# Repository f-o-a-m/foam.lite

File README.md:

# foam.lite

Deployed [here](https://f-o-a-m.github.io/foam.lite/)

## Latest Documentation

The latest documentation can be found on the [FOAM Developer Portal](https://f-o-a-m.github.io/foam.developer/foamlite/introduction.html).

## General Caveats
Due to weirdness with certain versions of Node and Spago, you'd ideally want to use the `v10.x` train of Node.
With nvm, this is `nvm install lts/dubnium && nvm use lts/dubnium`

## UI

To build the UI, make sure you have already build and deployed the dapp. When you're ready to build and serve the app, simply do

```bash
> npm i
> npm run bundle-app
> RELAYER_NFT=<contract adddress> npm run browserify
> npm run serve
```

The default address is [localhost:8080](localhost:8080)

## Quickstart to do an end-to-end flow

```shell
# Start a blockchain
make cliquebait-start

# Deploy the contracts
make deploy-contracts

# Bundle up the app to make it easier to pass arguments to it
# You could skip this step and run `spago -x <component>.dhall run -a "<args>"`
# instead of `node dist/<component>.js` in the future, but you'll have to do an
# `export PRIVATE_KEY=<copypaste the output>` as spago likes to add an annoying
# "[info] Build Succeeded" line to stdout sometimes. Also, because there's no way to tell
# spago that everything that follows is arguments for the app, you'll have to be
# wary of shell quoting/escaping issues in the `-a` arg to spago
make bundle

# Make an account that doesn't exist on the Ethereum node
PRIVATE_KEY=$(node dist/helper.js generate-private-key)
echo "The private key is ${PRIVATE_KEY}"

# Faucet the account with some of the FungibleToken we deployed, as well
# as some Ether to let it approve the RelayableNFT contract to spend its FungibleTokens
node dist/helper.js faucet --to-private-key ${PRIVATE_KEY} --also-ether

# Approve the RelayableNFT token to spend the account's balance (and automatically execute the approve() transaction on-chain)
node dist/helper.js approve --private-key ${PRIVATE_KEY} --submit --node-url "http://localhost:8545"

# Double check our balances
node dist/helper.js balance --private-key ${PRIVATE_KEY}

# Start a relayer server in the background. This is what the radios use to forward messages to the blockchain
# And what we will use to simulate radio messages being sent.
# It takes a couple of seconds to start up, so wait until you see "Started listening on http://0.0.0.0:3000"
node dist/server.js &
VALIDATE_ENDPOINT="http://localhost:3000/relay/validate"
SUBMIT_ENDPOINT="http://localhost:3000/relay/submit"

# Check the nonce that the blockchain expects our next message to have. If we've just created this account, this will probably be 0.
# You can use the output of this command as a `--nonce` argument for the `sign-*` helpers
node dist/helper.js nonce -p ${PRIVATE_KEY}

# Make a minting message that creates an "arbitrary" hello-world message
# Using relay-nonce 0, and paying 0.1 FT to the relayer, and simulate submitting it over
# the radio to our "validate" endpoint, to double check that it got encoded/signed correctly
node dist/helper.js sign-mint --private-key ${PRIVATE_KEY} -a 'Hello World!' --nonce $(node dist/helper.js nonce -p ${PRIVATE_KEY}) --fee-amount 1000000000000000000 --transmit ${VALIDATE_ENDPOINT}

# The exact same command, but to the "submit" endpoint, which will actually kick off a transaction on the blockchain
node dist/helper.js sign-mint --private-key ${PRIVATE_KEY} -a 'Hello World!' --nonce $(node dist/helper.js nonce -p ${PRIVATE_KEY}) --fee-amount 1000000000000000000 --transmit ${SUBMIT_ENDPOINT}

# We can have some fun now. Lets make a quick loop to send the current time as a relayed message on the blockchain every minute
while true; do
  the_message="It is now `date`"
  echo "sending \"${the_message}\" via relay"
  node dist/helper.js sign-mint --private-key ${PRIVATE_KEY} -a "${the_message}" --nonce $(node dist/helper.js nonce -p ${PRIVATE_KEY}) --fee-amount 1000000000000000000 --transmit ${SUBMIT_ENDPOINT}
  echo "waiting a minute" 
  sleep 60
done
```

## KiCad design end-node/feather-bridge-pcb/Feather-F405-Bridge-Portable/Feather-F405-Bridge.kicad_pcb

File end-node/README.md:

See the [latest documentation on the FOAM Developer Portal](https://f-o-a-m.github.io/foam.developer/foamlite/end-node.html) for more details and usage instructions.

**USE THIS FIRMWARE AT YOUR OWN RISK. BE MINDFUL OF LOCAL REGULATIONS PERTAINING TO USAGE OF THE RADIO SPECTRUM**

The firmware supplied here has been tested assuming all `make` commands are run with `TARGET_PLATFORM=FEATHER_F405`, which assumes an
Adafruit Feather STM32F405 Express and an RFM95W LoRa Radio FeatherWing.

While it is possible to compile for the `NUCLEO_F303RE` which can be used on the Nucleo-F303RE eval board with the SX1276MB1xAS mBed shield,
this version of the firmware with RelayableNFT functionality has not been tested on that device.

Shout outs to Trezor for making an awesome library of handy crypto utilities and all the hard work by the folks working on libsecp256k1 to make it microcontroller-friendly.

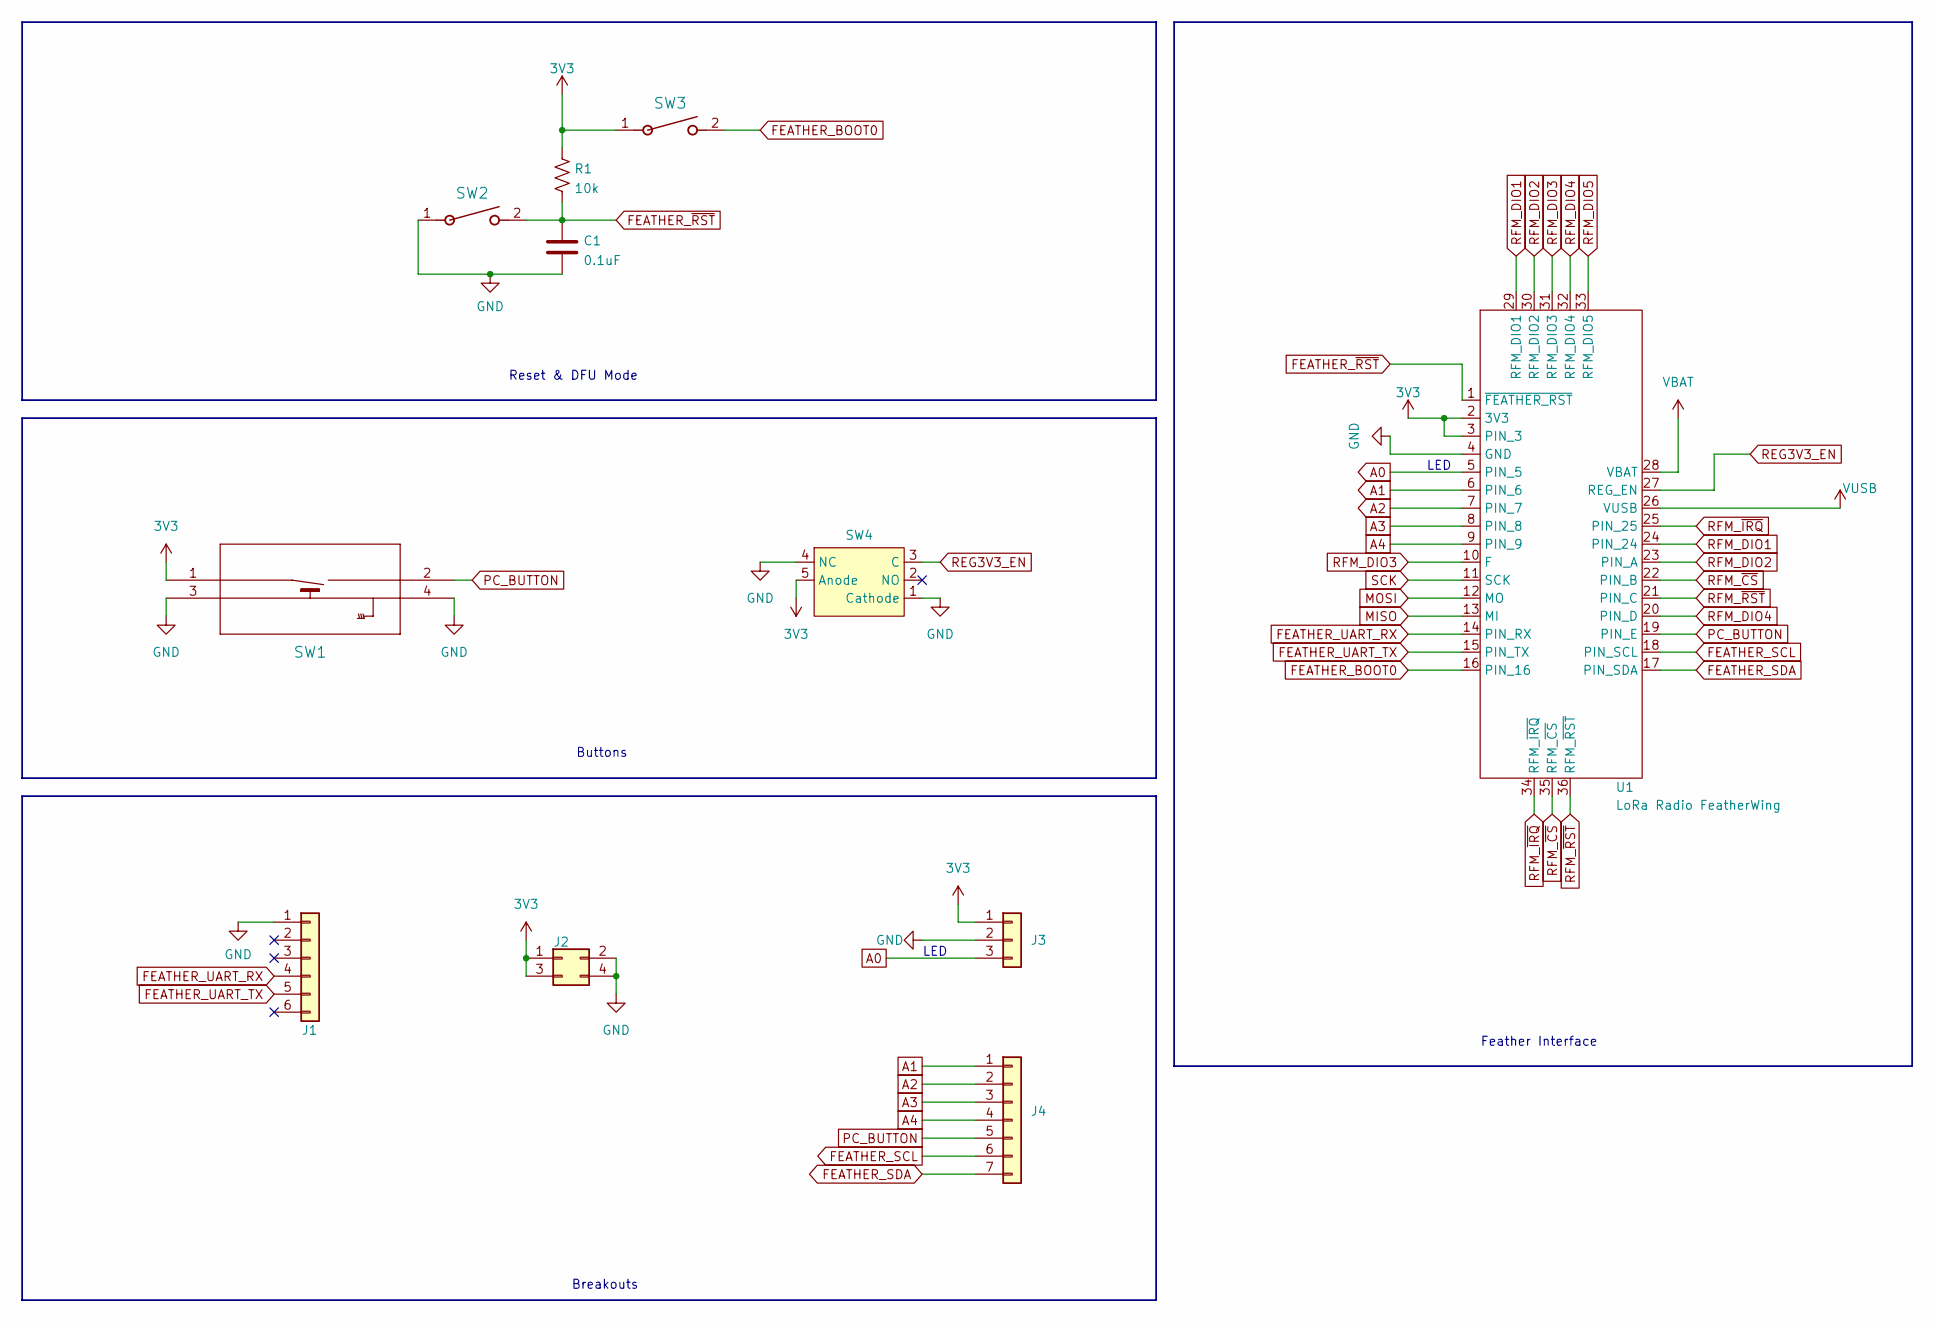
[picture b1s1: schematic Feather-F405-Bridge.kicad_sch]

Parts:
C1: 0.1uF; C_Disc_D3.0mm_W1.6mm_P2.50mm
J1: Conn_01x06; PinHeader_1x06_P2.54mm_Vertical
J2: Conn_02x02_Odd_Even; PinHeader_2x02_P2.54mm_Vertical
J3: Conn_01x03; PinHeader_1x03_P2.54mm_Vertical
J4: Conn_01x07; PinHeader_1x07_P2.54mm_Vertical
R1: 10k; R_Axial_DIN0207_L6.3mm_D2.5mm_P10.16mm_Horizontal
SW1: B3F-3152; SW_B3F-3150_OMR
SW2, SW3: TL1105MF160Q; SW_TL1105MF160Q
SW4: ELUMEETHQ7C22; ELUMEETHQC02
U1: LoRa Radio FeatherWing; Radio_FeatherWing_16x12+5+3

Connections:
3V3: J2.1, J2.3, J3.1, R1.1, SW1.1, SW3.1, SW4.5 (Anode), U1.2 (3V3), U1.3 (PIN_3)
A0: J3.3, U1.5 (PIN_5)
A1: J4.1, U1.6 (PIN_6)
A2: J4.2, U1.7 (PIN_7)
A3: J4.3, U1.8 (PIN_8)
A4: J4.4, U1.9 (PIN_9)
FEATHER_BOOT0: SW3.2, U1.16 (PIN_16)
FEATHER_SCL: J4.6, U1.18 (PIN_SCL)
FEATHER_SDA: J4.7, U1.17 (PIN_SDA)
FEATHER_UART_RX: J1.4, U1.14 (PIN_RX)
FEATHER_UART_TX: J1.5, U1.15 (PIN_TX)
FEATHER_~RST: C1.1, R1.2, SW2.2, U1.1 (~FEATHER_RST)
GND: C1.2, J1.1, J2.2, J2.4, J3.2, SW1.3, SW1.4, SW2.1, SW4.1 (Cathode), SW4.4 (NC), U1.4 (GND)
MISO: U1.13 (MI)
MOSI: U1.12 (MO)
PC_BUTTON: J4.5, SW1.2, U1.19 (PIN_E)
REG3V3_EN: SW4.3 (C), U1.27 (REG_EN)
RFM_DIO1: U1.24 (PIN_24), U1.29 (RFM_DIO1)
RFM_DIO2: U1.23 (PIN_A), U1.30 (RFM_DIO2)
RFM_DIO3: U1.10 (F), U1.31 (RFM_DIO3)
RFM_DIO4: U1.20 (PIN_D), U1.32 (RFM_DIO4)
RFM_DIO5: U1.33 (RFM_DIO5)
RFM_~CS: U1.22 (PIN_B), U1.35 (RFM_~CS)
RFM_~IRQ: U1.25 (PIN_25), U1.34 (RFM_~IRQ)
RFM_~RST: U1.21 (PIN_C), U1.36 (RFM_~RST)
SCK: U1.11 (SCK)
VBAT: U1.28 (VBAT)
VUSB: U1.26 (VUSB)

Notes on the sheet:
Reset & DFU Mode
Buttons
LED
Breakouts
Feather Interface

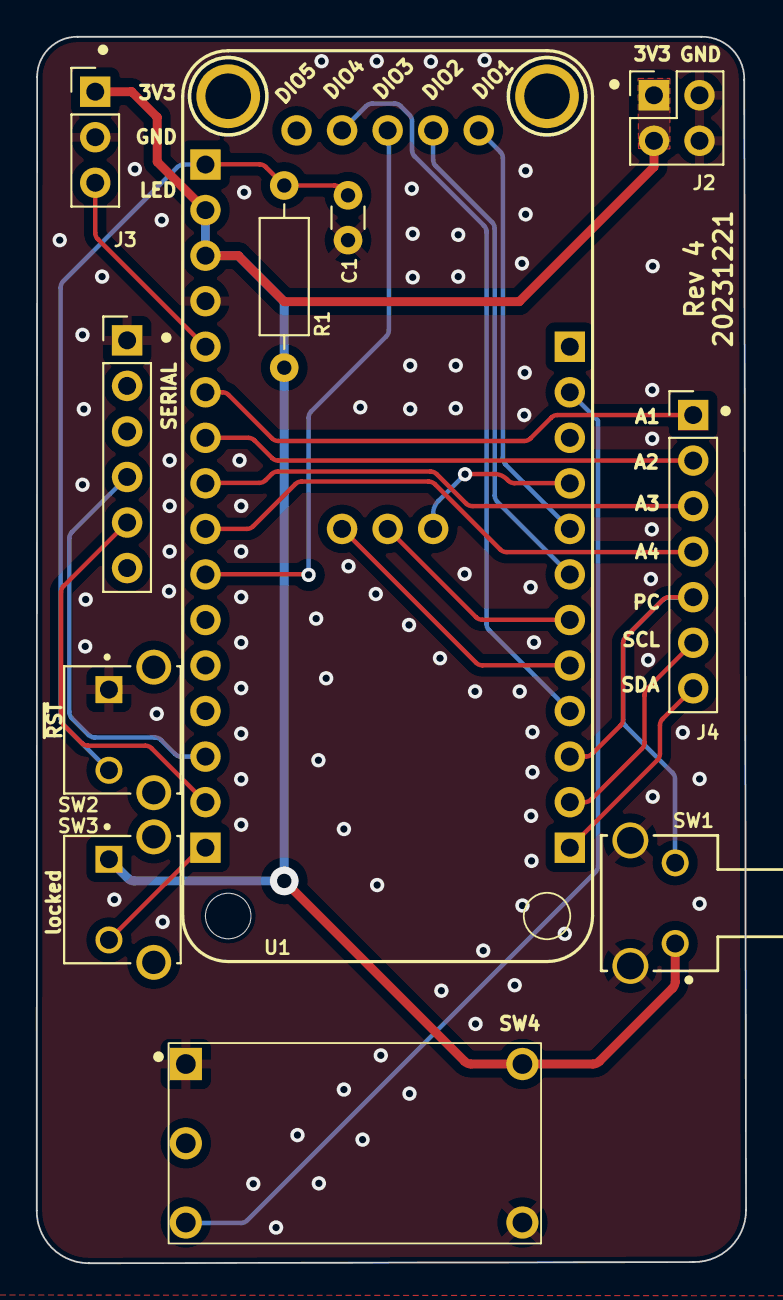
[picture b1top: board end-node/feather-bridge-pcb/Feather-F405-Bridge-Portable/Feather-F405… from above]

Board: 2 copper layers, 39.6 x 68.4 mm, 11 parts (0 on the bottom side), 22 nets.

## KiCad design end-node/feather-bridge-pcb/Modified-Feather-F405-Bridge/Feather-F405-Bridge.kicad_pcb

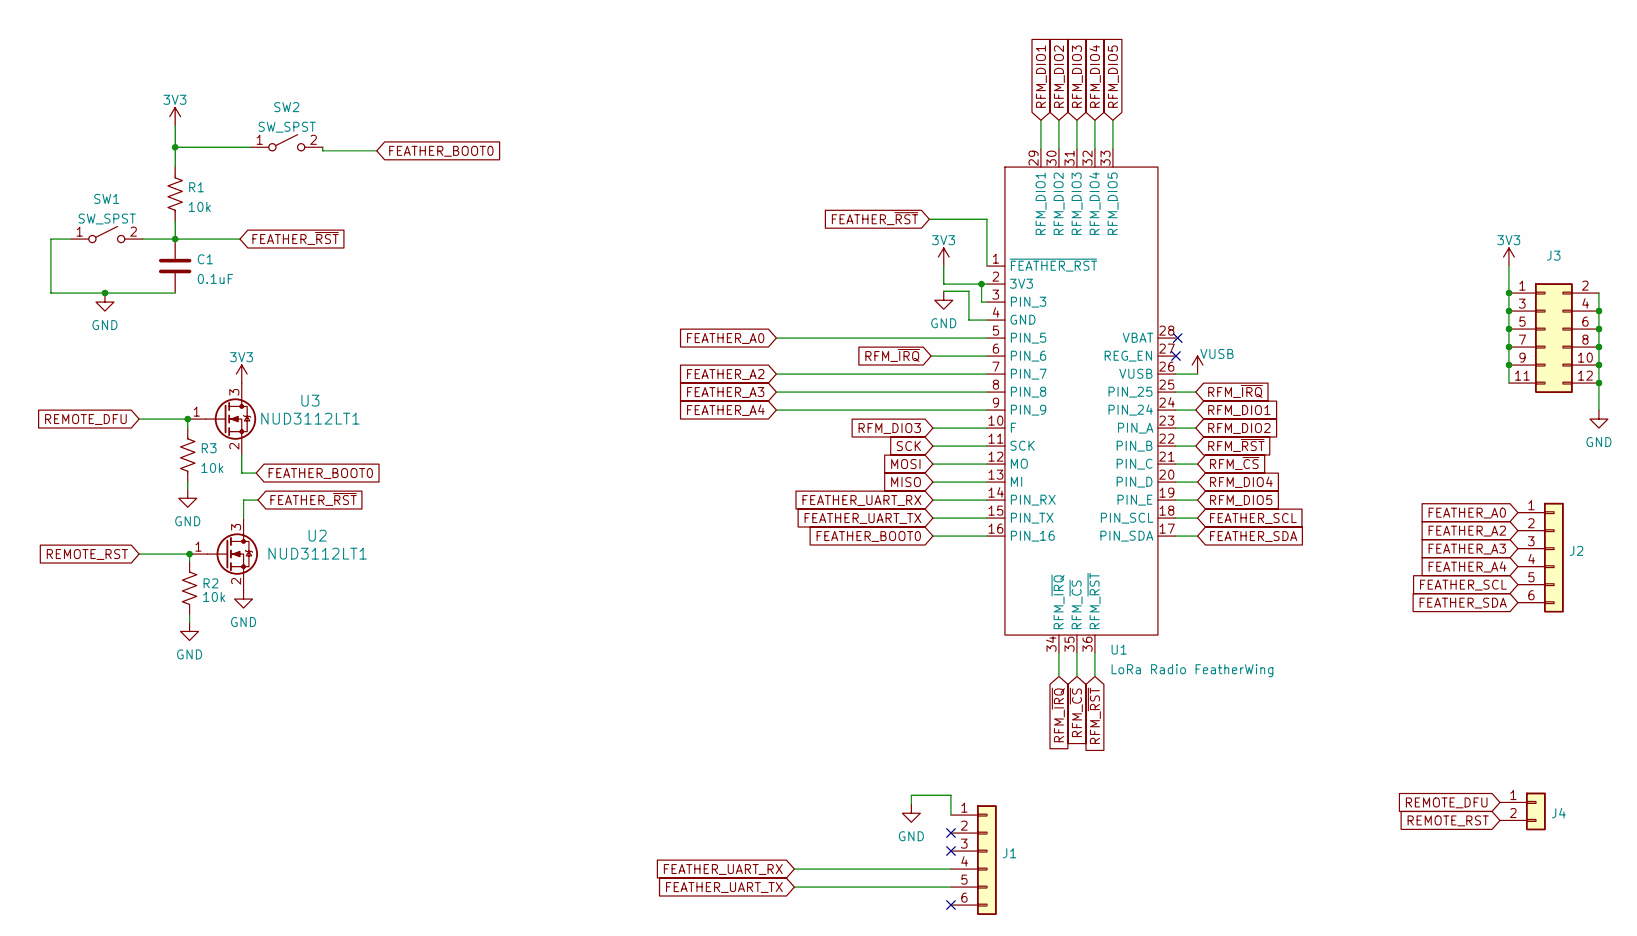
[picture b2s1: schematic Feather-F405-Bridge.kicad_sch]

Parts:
C1: 0.1uF; C_Disc_D3.0mm_W1.6mm_P2.50mm
J1, J2: Conn_01x06; PinHeader_1x06_P2.54mm_Vertical
J3: Conn_02x06_Odd_Even; PinSocket_2x06_P2.54mm_Vertical_No_Index
J4: PinHeader_1x02_P2.54mm_Horizontal
R1, R2, R3: 10k; R_Axial_DIN0207_L6.3mm_D2.5mm_P10.16mm_Horizontal
SW1, SW2: SW_SPST; SW_PUSH_6mm_THT
U1: LoRa Radio FeatherWing; Radio_FeatherWing_16x12+5+3
U2, U3: NUD3112LT1; SOT-23

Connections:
3V3: J3.1, J3.3, J3.5, J3.7, J3.9, J3.11, R1.1, SW2.1 (A), U1.2 (3V3), U1.3 (PIN_3), U3.3 (D)
FEATHER_A0: J2.1, U1.5 (PIN_5)
FEATHER_A2: J2.2, U1.7 (PIN_7)
FEATHER_A3: J2.3, U1.8 (PIN_8)
FEATHER_A4: J2.4, U1.9 (PIN_9)
FEATHER_BOOT0: SW2.2 (B), U1.16 (PIN_16), U3.2 (S)
FEATHER_SCL: J2.5, U1.18 (PIN_SCL)
FEATHER_SDA: J2.6, U1.17 (PIN_SDA)
FEATHER_UART_RX: J1.4, U1.14 (PIN_RX)
FEATHER_UART_TX: J1.5, U1.15 (PIN_TX)
FEATHER_~RST: C1.1, R1.2, SW1.2 (B), U1.1 (~FEATHER_RST), U2.3 (D)
GND: C1.2, J1.1, J3.2, J3.4, J3.6, J3.8, J3.10, J3.12, R2.1, R3.2, SW1.1 (A), U1.4 (GND), U2.2 (S)
MISO: U1.13 (MI)
MOSI: U1.12 (MO)
REMOTE_DFU: J4.1, R3.1, U3.1 (G)
REMOTE_RST: J4.2, R2.2, U2.1 (G)
RFM_DIO1: U1.24 (PIN_24), U1.29 (RFM_DIO1)
RFM_DIO2: U1.23 (PIN_A), U1.30 (RFM_DIO2)
RFM_DIO3: U1.10 (F), U1.31 (RFM_DIO3)
RFM_DIO4: U1.20 (PIN_D), U1.32 (RFM_DIO4)
RFM_DIO5: U1.19 (PIN_E), U1.33 (RFM_DIO5)
RFM_~CS: U1.21 (PIN_C), U1.35 (RFM_~CS)
RFM_~IRQ: U1.6 (PIN_6), U1.25 (PIN_25), U1.34 (RFM_~IRQ)
RFM_~RST: U1.22 (PIN_B), U1.36 (RFM_~RST)
SCK: U1.11 (SCK)
VUSB: U1.26 (VUSB)

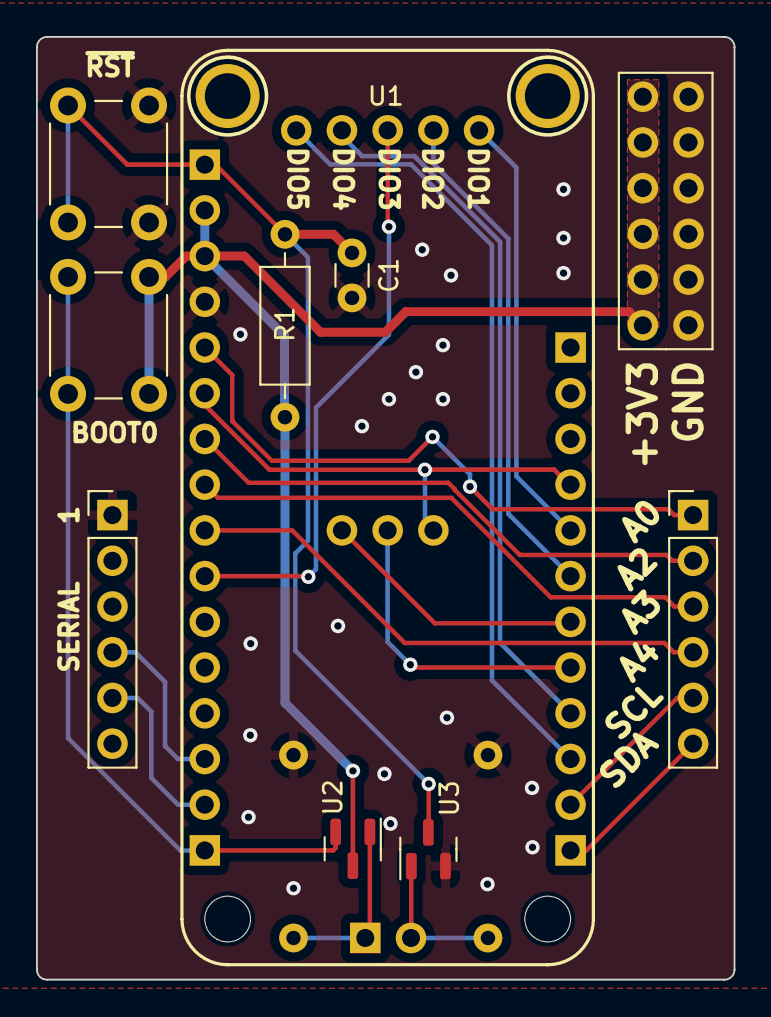
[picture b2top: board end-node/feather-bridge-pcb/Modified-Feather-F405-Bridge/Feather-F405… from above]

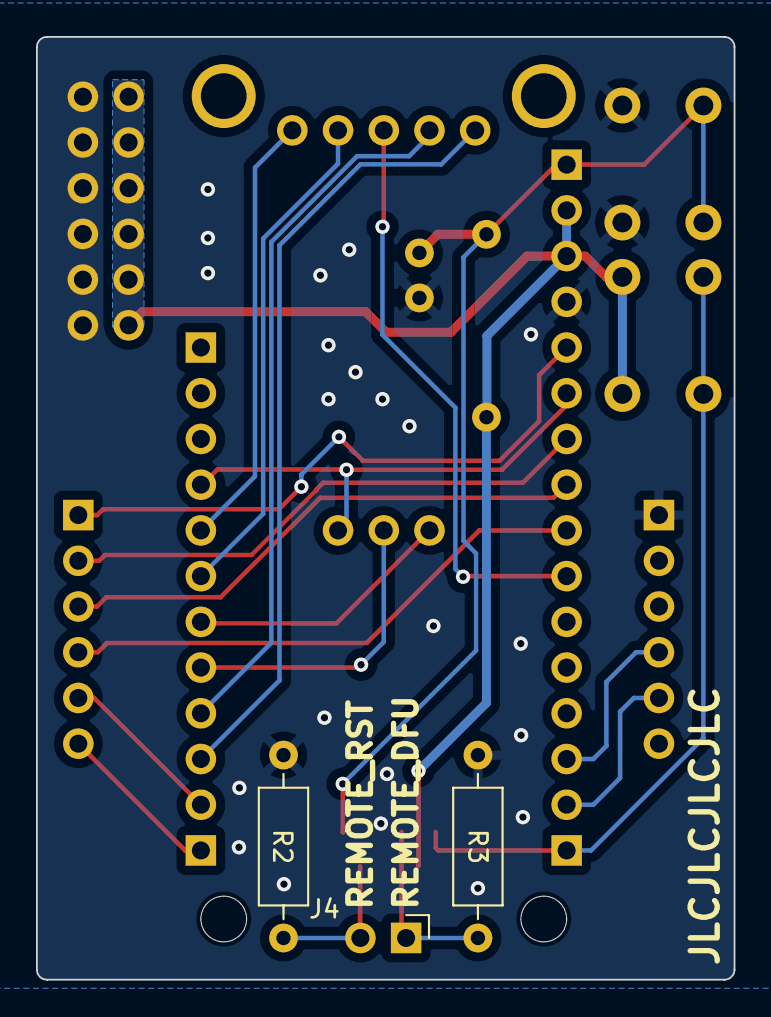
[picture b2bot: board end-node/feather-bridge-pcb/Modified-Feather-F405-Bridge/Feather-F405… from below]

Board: 2 copper layers, 38.8 x 52.4 mm, 13 parts (3 on the bottom side), 22 nets.

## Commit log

2020-10-08 add a message type, add transferRelayed, support signing with purescript-eth-core instead of web3
2020-10-08 clean redundant imports
2020-10-08 add homepage to bower.json
2020-10-09 added package lock to ignore file
2020-10-12 builds
2020-10-12 switch to spago
2020-10-12 make dapp and app folders
2020-10-12 added travis file
2020-10-12 install chanterelle as dev dep
2020-10-12 try with global chanterelle
2020-10-12 use local chanterelle
2020-10-12 force compile chanterelle
2020-10-12 more minimal dhall file
2020-10-12 proper names in dhall files
2020-10-12 app builds
2020-10-12 added dist
2020-10-12 gitignore
2020-10-12 app basics
2020-10-12 remove unused css
2020-10-12 actually emit the event
2020-10-13 generalize toethsignedmessage
2020-10-13 mocking data
2020-10-13 txHash
2020-10-13 make data module
2020-10-13 added room for subscription to web3
2020-10-13 event sourcing compiles
2020-10-13 added config module
2020-10-13 ENV vars works with envify
2020-10-14 UI responsive
2020-10-16 stuff for the relay serveR
2020-10-18 tokenURI -> tokenData (sol)
2020-10-18 gitignore dapp/Contracts/
2020-10-18 tokenURI -> tokenData (purs dapp/test)
2020-10-18 add phony targets, fix build->build-dapp
2020-10-18 fix make serve-app
2020-10-19 helper CLI utility, purescript-eth-core v6.1.0
2020-10-20 add helper spago file which was missing, and add POST support to helper
2020-10-21 add getter for tokenData in RelayableNFT.sol
2020-10-21 print the whole spec config, including private account private key
2020-10-21 add type to interpreted a signed message, make signed message parsers more strict on parsing messages (i.e., check theres no leftover data)
2020-10-21 make json encoding of interpretedmessage less ambiguous, implement decode helper subcommand
2020-10-21 sign transactions with non-web3 account in a self-contained manner, and remove the super dangerous approveForAll in FungibleToken that the tests all depend on
2020-10-21 read scanned values serially
2020-10-22 add support for signing transactions without a wallet on the node
2020-10-22 automatically use first non-st-link tty
2020-10-22 scan in loop and messages on screen under stderr
2020-10-22 executable serial_read
2020-10-22 ledger support / rinkeby deployment
2020-10-22 add udev-dev so travis can build with ledger support
2020-10-24 Make LedgerSupport a little more idiotproof, generalize signABIFn to arbitrary txns
2020-10-24 add endpoints to server that will support foam lite OTA nonce/tx status
2020-10-24 stuff in package.json/Makefile to help deployment, quickstart in README + helper enhancements to support it
2020-10-26 add package lock to ignore
2020-10-26 Added tray for logging
2020-10-26 fix npm run backend-dist
2020-10-26 switch to toast
2020-10-26 use toast if filter ends
2020-10-26 basic map component compiles
2020-10-26 added beacon.png
2020-10-26 map and map container
2020-10-26 allow CONTRACT_ADDRESS env to spin up server faster, fix warning in helper
2020-10-27 basic map with no data
2020-10-27 default beacon
2020-10-27 change default zoom level
2020-10-27 copy modules from foam.vis
2020-10-27 Ping Layer
2020-10-27 added ping purs files
2020-10-27 removed all files
2020-10-27 make root component the primary event listener
2020-10-28 initialize root component
2020-10-28 trace points as they come through
2020-10-28 wiring works
2020-10-28 Webpack seems to work with deck.gl. Needs testing
2020-10-28 Devserver on 0.0.0.0
2020-10-28 Logging from entrypoint
2020-10-28 print log in entrypoint before app starts
2020-10-29 Cleanup
2020-10-29 compiles without warnings
2020-10-29 compiles without warnings but no animations
2020-10-29 keep an increasing clock
2020-10-30 Works. Could use some polish in terms of design
2020-10-30 Kristoffer/ping (#15)
    * copy modules from foam.vis
    * Ping Layer
    * added ping purs files
    * removed all files
    * Webpack seems to work with deck.gl. Needs testing
    * Devserver on 0.0.0.0
2020-11-02 Added second point
2020-11-03 put pings on a timeout
2020-11-11 Added github pages job
2020-11-11 master -> main
2020-11-11 Deploy f-o-a-m/foam5g to github.com/f-o-a-m/foam5g.git:gh-pages
2020-11-11 Actually do the bundle for pages
2020-11-11 much smaller webpack output
2020-11-11 Added ENV vars to travis
2020-11-11 Added google analytics
2020-11-11 Renamed to foam.lite
2020-11-11 Hardcoded GA token
2020-11-11 Deploy f-o-a-m/foam.lite to github.com/f-o-a-m/foam.lite.git:gh-pages
2020-11-14 multiple mime types support for more optimal relay forwarding
2020-11-14 nodetrout polymorphic content types
2020-11-17 frontend++
2020-11-17 frontend++ (#20)
2020-11-17 backfilling support
2020-11-17 fix toast padding
2020-11-17 clean warnings
2020-11-17 rearrange table rows to be more information dense
2020-11-17 increase historical filter size
2020-11-17 remove superfluous console.logs
2020-11-17 better backfill status messages
2020-11-18 Make RNFT Ownable so we can update baseURI in the future
2020-11-18 support env ledger account offset when deploying
2020-11-18 more informative logging when FungibleToken is used from an existing contract
2020-11-18 remove dependency on Ocelot, vendoring it the two functions we still used into UI.Utils
2020-11-18 print envs when webpacking
2020-11-18 table formatting tweaks
2020-11-18 comment out looking at tokendata for now, we dont need it
2020-11-18 add support for showing backfill progress, to be used when we canknown an event filter's block number outside of an event handler
2020-11-21 move styles to their own directory, add SCSS pipeline, put stuff in place for dynamic token icons
2020-11-21 fix autodeploy to use our deployed contracts
2020-11-21 cleaup warnings -- dont load token icon CSS as rendering them is disabled due to browser bugs
2020-11-21 cleanup some warnings
2020-11-21 remove unused colors from tailwind, shrinking main CSS by a whopping 2MB
2020-11-21 accidentally commit debug print of default colors
2020-11-22 fix relative paths for assets, use cp -v to see why deployed artifacts arent getting built in
2020-11-23 Bump to node v10.x to give us more headroom with dependencies
2020-12-08 change readme image
2020-12-08 readme tweaks
2021-11-10 Running draft of Lora gateway implementation
2021-11-13 Lora bridge: improve code style and eliminate warnings
2021-11-13 move mkEnv and readArtifacts to a helper module in DApp.Support, cleanup redundant imports from the refactor
2021-11-13 make DApp.Support functions MonadAff because its easy and clean
2021-11-13 make fromMaybe ... PACKET_RECEIVER_PORT more readable
2021-11-13 add support for estimating gas of relay Txs
2021-11-13 export estimate utils, add to AppEnv
2021-11-15 Lora: dry run messages and logging
2021-11-16 Improvements to code and error handling
2021-11-17 Add PI installation documentation
2021-11-17 fix burn tests to handle new revert behavior in some clients/contract versions
2021-11-24 Improve PI documentation
2021-12-11 Create Sjenica1
    Authorized mit meine Account Sjenica1 github.com reufrujevic750@gmail.com
2022-02-01 Added upload of foam.lite.tgz to travis job
2022-02-01 Forgot to hit save
2022-02-01 token
2022-02-01 Lora + build artifacts as releases (#26)
    * Running draft of Lora gateway implementation
    * Lora bridge: improve code style and eliminate warnings
    * move mkEnv and readArtifacts to a helper module in DApp.Support, cleanup redundant imports from the refactor
    * make DApp.Support functions MonadAff because its easy and clean
    * make fromMaybe ... PACKET_RECEIVER_PORT more readable
    * add support for estimating gas of relay Txs
2022-02-01 Update PI.md
    Added instructions for using GH releases instead of building on desktop
2022-02-15 import firmware, link to dev portal
2023-05-03 add modified feather_bridge_files
2023-05-08 cleanup schematic
2023-05-08 Remove UART RX/TX crossover SB, fix resistor footprints, add separate header for remote dfu/rst, fancy logo
2023-05-08 tweak some lines for future changes with BLE
2023-05-08 rename + cleanup
2023-05-09 misc aesthetic tweaks
2023-05-09 final production outputs
2023-12-20 updated bridge pcb for portable feather Tx
2023-12-20 remove unwanted file
2024-01-26 changed receptacle pins from 315 to 801 series
